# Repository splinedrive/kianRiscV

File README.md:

**RISC-V Linux/XV6 SoCs**
================================
**KianV SV32 (MMU) RV32IMA Zicntr Zicsr Zifencei SSTC Linux/XV6
SoC**, a robust RISC-V design with full virtual memory support, seamlessly
running Linux and XV6.
[KianV SV32 RV32IMA SoC](https://github.com/splinedrive/kianRiscV/tree/master/linux_socs/kianv_mc_rv32ima_sv32)

**Linux ASIC Designs**
======================
Check out the nice RISC-V uLinux ASIC I built—see the article at 
[FOSSI Foundation](https://fossi-foundation.org/blog/2025-01-14-ecl82).

```
 __  __ __               ___ ___ _____   __
|  |/  |__|.---.-.-----.|   |   |     |_|__|.-----.--.--.--.--.
|     <|  ||  _  |     ||   |   |       |  ||     |  |  |_   _|
|__|\__|__||___._|__|__| \_____/|_______|__||__|__|_____|__.__|
```

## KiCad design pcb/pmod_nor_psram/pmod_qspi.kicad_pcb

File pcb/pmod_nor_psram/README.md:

A PMOD which combines flash and NOR on a PCB to boot Linux on iCE40s and other FPGAs that do not provide memory.

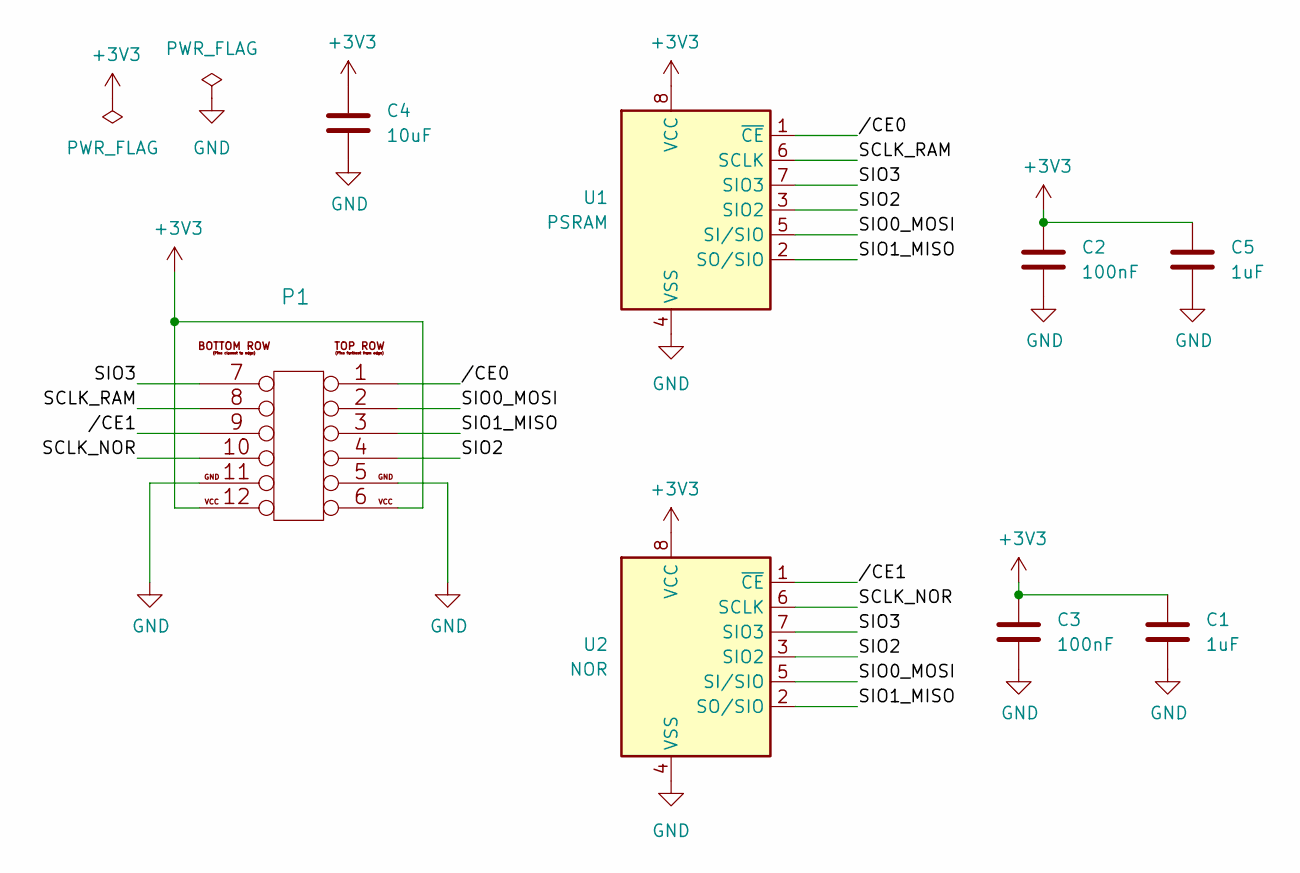
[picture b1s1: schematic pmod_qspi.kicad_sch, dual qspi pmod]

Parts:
C1, C5: 1uF; C_0603_1608Metric
C2, C3: 100nF; C_0603_1608Metric
C4: 10uF; C_0603_1608Metric
P1: PMOD-Device-x2-Type-Generic-Alt; pmod_pin_array_6x2
U1: PSRAM; SOIC-8_3.9x4.9mm_P1.27mm
U2: NOR; SOIC-8_5.275x5.275mm_P1.27mm

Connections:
+3V3: C1.1, C2.1, C3.1, C4.1, C5.1, P1.6, P1.12, U1.8 (VCC), U2.8 (VCC)
/SCLK_NOR: P1.10, U2.6 (SCLK)
/SCLK_RAM: P1.8, U1.6 (SCLK)
/SIO0_MOSI: P1.2, U1.5 (SI/SIO), U2.5 (SI/SIO)
/SIO1_MISO: P1.3, U1.2 (SO/SIO), U2.2 (SO/SIO)
/SIO2: P1.4, U1.3 (SIO2), U2.3 (SIO2)
/SIO3: P1.7, U1.7 (SIO3), U2.7 (SIO3)
//CE0: P1.1, U1.1 (~CE)
//CE1: P1.9, U2.1 (~CE)
GND: C1.2, C2.2, C3.2, C4.2, C5.2, P1.5, P1.11, U1.4 (VSS), U2.4 (VSS)

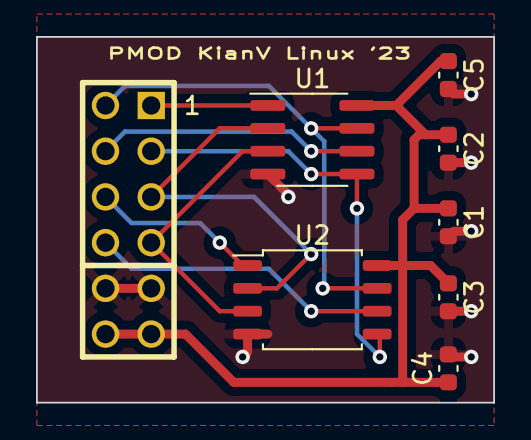
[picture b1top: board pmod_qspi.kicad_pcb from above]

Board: 4 copper layers, 25.4 x 20.3 mm, 8 parts (0 on the bottom side), 10 nets.

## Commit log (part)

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2021-09-25 initial kianv riscv rv32im cpu
2021-09-25 fix kianv uart in syscalls
2021-09-26 toolchain description
2021-09-26 fixed icefun soc
2021-10-20 ascii cast you can play with asciinema play 443631.cast
2021-11-12 BrunoLevy Added Sylvain Lefebvre's animated Julia example. for kianv riscv
2021-12-09 mentioning Bruno for scripts and some firmware
    Taken from https://github.com/BrunoLevy/learn-fpga and adjusted for my soc
2021-12-19 add toolchain build script for rv32im!
2021-12-20 compiler default to -Os
2021-12-21 renamed view regs in multiplier and divider units into abs (absolute value)
2021-12-21 fix pi example
2021-12-22 added sdd1331 gfx 3d lib and 3d demos: rotating house and rotating cube
2021-12-23 rewrite init oled sequential code from userspace to switch to 256 color mode added support for color 256 mode in gfx_lib.h cube and house 3d demos flushing framebuffer in 256 mode to have half traffi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
    Please compile with -O3 e.g. icoboard looks like
    ./flash_firmware.sh ico spi_nor2sram.ld main_cube3d_rotate.c -O3
2021-12-25 support for colorlighti5 ./flash_firmware.sh colori5 spi_nor2bram_colori5.ld main_raytrace.c -O3
2021-12-25 fix colorlighti5
2021-12-25 oh colorlight was working with 120MHz and 30MHz spi but switch to some more reliable back
2021-12-31 added gpio interface with 8 pins, very easy to expand!
    expanding in pin assigment and soc interface GPIO_NR gives the number of
    pins
2022-01-01 gpio is able to handle max. 32 ports, just assign in .pcf or .lpf gpio[0] ... gpio[31]
    .pcf and .lpf have no pullups or downs! For spi you should use pullups
    and you have to touch .pcf or .lpf files.
2022-01-01 one file fat16/32 example adapted from ultraembedded https://github.com/ultraembedded/fat_io_lib
    please pullup the gpios in pcf or lpf file
2022-01-03 8 gpios for icefun
2022-01-04 gpio description
2022-01-09 Colorlighti5
2022-01-17 fix makefile for newer yosys
2022-01-27 kianRiscV based TangNano-9K-example
2022-01-27 attosoc
2022-01-28 rework of mul/div signal handling, save reg
2022-02-06 attosoc makefile fix
2022-03-24 direct mapping cache c++/verilog
    verilog is productive
2022-04-18 Revert "quick fix of luipc obsolete kianv..."
    This reverts commit be28545578138b2487b788571366dca571d8320b.
2022-04-26 initial commit for my new cpu based on multicycle harris design rule
    first commit alu
2022-05-01 New KIAN-V RISC-V multicycle hierachical Harris2 designed CPU with HDMI SOC
    - current fpga: ulx3s, colorlighti9, colorlighti5 and icebreaker.
    - RISC-V unittest verified CPU
2022-05-01 Revert "remove pictures"
    This reverts commit b2acc842013035d77a446242181c16ca9d28e3e8.
2022-05-02 added firmware for kianv RISC-V soc pmod led matrix hack for machdyne 4x4 matrix led
    https://github.com/machdyne/matrix
2022-05-03 makefile for icebreaker
2022-05-06 remove some warnings in CPU
2022-05-06 - icefun fpga soc config
    - RiscVPong pre-compiled firmware + c source code
2022-05-06 added for kianv multicycle cpu attosoc for ulx3s/ecp5
2022-05-10 fix soc bin for icefun, add ld nor script for ecp5
2022-05-12 fixed hdmi
2022-05-15 fix for hdmi
2022-05-16 revert old description from simple kianv edition
2022-05-20 roms for arty7, nexysa7 and nexysvideo
    kianriscV hdmi soc with 3d cube running hdmi demo
2022-05-28 fix but it will make no differ, addition takes 1 cycle
2022-05-29 added flash image for icestick soc + running oled sdd1331 seed demo firmware
    plug digilent oled pmod on icestick
2022-06-06 fix ld firmware script
2022-06-10 added dma controller
    `define DMA_CONTROLLER to enable it
    in firmware activate #define DMA, default enabled
    fw is still a hack, coz I like only logic design
2022-06-10 added dma controller
2022-09-23 add genesys2 support with 200MHz
2022-09-30 add cmoda7-35t digilent fpga board
2022-10-10 kian riscv single cycle cpu with uart and able to run as a soc on genesys2
    and Vivado files
2022-10-16 rework of single cycle cpu decoder
2022-11-06 rename project folder of Pipelined RISCV cpu
2022-11-06 pipelined picture
2022-12-02 new firmware works without raw mode tty
2022-12-10 could reduce 1 cycle. prevalid the instruction fetch: in mem wb, alu wb, mul/div wb and csr wb
2022-12-11 need some resources for icestick
2022-12-28 kian riscv running micropython with 1000000 Baud and 32 MByte SDRAM
2023-01-03 missed ice40hx1k linker script
2023-02-16 fix copyright
    fix qqspi
    added ulx3s, colorlighti5_i9 demosocs and sdram bytewise test firmware
    ulx3s-85f: 32MByte
    colorlighti5_i9: 8MByte
2023-02-17 latest micropyton snapshot for kian riscv emulator and reference to repo
    https://github.com/splinedrive/micropython/tree/kianv_riscv_soc
2023-04-23 no cache
2023-04-23 added <soc_variant>
    soc_12f_70mhz.bit
    soc_45f_70mhz.bit
    soc_85f_70mhz.bit
2023-04-24 A uLinux RISC-V RV32IMA SoC is booting Linux. Flash instructions can be found in demo/README.md. Build the SoC using the script: ./build_ulx3s.sh.
2023-04-24 added bootloader. KianV don't need a bootrom in bram
    PC starts at 0x20000000 after RESET
2023-04-24 darkriscv comment
2023-04-24 added linux soc description
2023-04-26 fix access fault, added sdram
2023-05-08 fix qqspi
2023-05-16 update README.md with KianVLinux ASCII-LOGO
2023-05-20 Fixed issue where 9 instructions were skipped after
    reset and zero-containing instructions were retrieved.
    Removed unnecessary 'op == 0' condition statement in main_fsm."
2023-05-20 A few subtleties
2023-05-23 added flash script for icesugar
2023-05-25 Revert "update led pc"
    This reverts commit 6cd97199732e19fe426a237daee79e889775aa7a.
2023-05-27 I changed the QQSPI controlle. My ULX3S 3.1.7 had an issue with it,
    but currently, only SPI mode works with it.
    You should disable qspi when you have an issue.
2023-05-29 add softlink for bootloader
2023-05-30 improve build script
2023-06-11 update of my certs
2023-07-30 Added Linux SoC flash binary for TangNano20K; can now be flashed using
    openFPGALoader --board=tangnano20k --external-flash -f kianVLinuxRiscvSocTangNano20K.bin
2023-07-31 Migrating from KianV RISC-V uLinux SoC to Tang Nano 20K with project files.
    Or simply flash the binary and boot into Linux with 2mbaut UART speed
    using
    curl -sL https://github.com/splinedrive/kianRiscV/raw/master/linux_socs/kianv_harris_mcycle_edition/demo/tangNano20K/kianVLinuxRiscvSocTangNano20K.bin \
    | openFPGALoader --board=tangnano20k --file-type ext --external-flash -f
2023-09-09 fix clk frequency in dts
2023-10-06 Fix AMO kernel locking issue and rename signals
    - Resolved the atomic memory operation (AMO) locking problem in the kernel.
    - Renamed several signals for better clarity and consistency.
2023-10-06 new title picture
2023-10-25 fix software interrupt
2023-11-09 split registerfile into 16 for gowin synthesis
2023-11-12 uLinux KianV RV32IMA uLinux SoC for kuchen machdyne
2024-01-01 fix pc calculation
2024-02-11 added icefun pcf
2024-02-26 fix sdram ctrl logic
2024-03-01 use hq sdcards
2024-03-02 added sdcard image for 65mhz for 45f and 85f ulx3s
2024-03-02 update README.md sv32 demo
2024-04-05 Implementation of a RISC-V RV32IMA SV32 Linux SoC 'KianV'.
2024-04-17 Fix rdata to reset to 0, resolving simulation issues with Icarus Verilog.
2024-04-18 Migrate KianV SV32 RV32IMA Linux SoC to kernel 6.8.1
2024-04-21 picture of supported network chips
2024-05-03 migration to kernel 6.8.9
2024-05-13 Migrate to mainline Linux kernel 6.9
2024-05-17 Migrate to mainline Linux kernel 6.9.1
2024-05-25 Migrate to stable Linux kernel 6.9.2
2024-06-01 Migrate to mainline Linux kernel 6.9.3
2024-06-16 Migrate to stable Linux kernel 6.9.5
2024-06-23 Commit demo images for xv6 on KianV RISC-V SoC. These include the necessary binaries to boot and run the system on the Colorlight i5 board.
2024-06-27 Migrate to stable Linux kernel 6.9.7
2024-07-05 Migrate to stable Linux kernel 6.9.8
2024-07-18 Migrate to stable Linux kernel 6.9.10
2024-07-24 Add TinyTapeout TT05 ASIC with KianV RV32IMA and uLinux SoC support
2024-08-03 Migrate to stable Linux kernel 6.10.3
2024-08-09 update tt05 ulinux ASIC SoC
2024-09-16 update of console image
2024-09-16 migrate to mainline linux kernel 6.11
2024-09-19 add kianv logos
2024-09-30 You'll own nothing and be happy!
2024-11-16 Refactor Kianv SoC and Bootloader for Latest xv6 Integration
    - Updated bootloader files (`Makefile`, `bootloader.c`, `firmware.bin`, `.elf`, `.hex`) for compatibility and optimizations.
    - Refactored BRAM, CLINT, PWM, QQSPI, and SPI modules for improved functionality.
    - Added support for PLIC (Platform-Level Interrupt Controller) to enhance interrupt management.
    - Updated SV32 virtual memory support to align with supervisor-level extensions.
    - Adjusted CSR handling (`csr_exception_handler.v`, `csr_utilities.vh`) and datapath for extended RISC-V functionality.
    - Incorporated changes to align with latest `xv6` from commit `de247db5e6384b138f270e0a7c745989b5a9c23b`.
2024-11-19 fix build ulx3s
2024-11-25 Remove synthesis files.
2024-11-28 default baudrate is 2e6
2024-12-03 Update Kianv DTS: Refined ISA and MMU properties for RV32IMA_sv32
2024-12-03 updating readmes
2024-12-06 Increase SD Card Command Retries
    - Updated `MAX_RETRIES` from 2 to 8 in the bootloader's SD card handling code.
    - Improves robustness in scenarios where commands need additional retries.
2024-12-08 Fix Quartus generator loop in gpio.v
2024-12-23 ci: action to build the OS
2024-12-23 ci: action to build the rv32ima sv32 linux
2024-12-24 Add TinyTapeout TT06 KianV RV32IMA uLinux ASIC SoC
2024-12-24 add xv6 ci build
2024-12-24 Fix a typo in Dockerfile comment
2024-12-24 added reboot, shutdown, qemu host
    ../host/bin/qemu-system-riscv32 -M virt -bios none -kernel Image -append "rootwait root=/dev/vda ro" -nographic -cpu rv32,mmu=off
2024-12-25 fix typo in Dockerfile, thanx to urish
2024-12-26 add pwm module
2024-12-30 fix sv32
2024-12-30 enable kernel v6.13-rc5
2025-01-30 Optimize ALU Zero Flag Calculation
2025-02-07 added tt07-KianV-RV32E-Baremetal-Audio-SoC ASIC
2025-02-07 Some other ASICs I have designed, tested, and that physically exist
2025-03-18 CI: Include fs.img in GitHub Actions build artifacts
2025-04-22 get rid of this shit
2025-05-01 Aktualisieren von README.md
2025-07-28 xv6: Port latest upstream commit 2a39c5af
    Ported changes from xv6-riscv upstream (commit 2a39c5af63906b3dbd0db58b9f6846ad70f4315d):
2025-08-21 div/mul: refactor for better timing & correctness
    - Add pipelined power-of-two fast path (>>k, (divisor-1) mask)
    - Use CLZ/CTZ helpers for early-exit/bitlength
    - Hint DSP for subtract; reduce barrel-shifter usage
2025-08-24 refactor(div,mul)
2025-09-03 added kianv soc png
2025-09-06 dram: mt48lc16m16a2_ctrl: JEDEC guards; TCH_NS→TMRD_CYC
    - Add tRAS/tRC/tRRD counters to prevent PRE/ACT and inter-bank ACT hazards
    - Replace ns-based TCH_NS with cycle-based TMRD_CYC (≥2 per JEDEC)
    - Clamp tRP/tRCD ≥2 cycles; widen wait counter for high clocks
    - Keep open-row policy and refresh scheduler; parametrize MR fields
    BREAKING: TCH_NS removed. Use TMRD_CYC (default 2).
2025-09-08 Set default frequency for icepi-zero to 60 MHz
2025-09-16 sfence.vma revisit privilege
2025-09-17 uLinux SoC: disable qspi by default
2025-09-26 spi: kianv: Consolidate three SPI drivers into unified driver
    - Reduce code duplication and maintenance overhead
2025-09-28 n-way assoc RAM ctrl w/ RR, random, LRU eviction; iTLB/dTLB/iCache/dCache default 4-way updated
2025-09-29 icepi-zero 55 MHz
2025-10-02 refactor(cpu): cleanup and reorganization
2025-10-03 add missing verilog modules
2025-10-03 fix(ulinux/uart): set default baudrate to 115200
2025-10-10 fix Makefile
2025-10-10 add: IcePi Zero support version 1.3 (default)
    - Updated FPGA build script to support IcePi Zero (ECP5)
    - Added default LPF file: icepi-zero-v1_3.lpf
    - Usage: ./build.sh [lpf_file]
    Example: ./build.sh icepi-zero-v1_2.lpf
    Default: ./build.sh icepi-zero-v1_3.lpf
2025-10-29 kianv_mc_rv32ima_sv32: cleanup FSMs, fix SPI timing, adjust bootloader init delay
    sv32: clean up internal signal naming and FSM; register memory access
    bootloader: Move initial delay before hardware register configuration in bootloader
    spi: fix transfer timing and FSM logic

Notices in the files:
pcb/pmod_nor_psram/pmod_qspi.kicad_sch:
(c) 2023 logic kian,  @twitter splinedrive
